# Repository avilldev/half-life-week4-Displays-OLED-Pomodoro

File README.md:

# BrainBreeze

A custom-built desktop hardware companion that tracks your study sessions and monitors your room's environment.

View the project on the [Half Life page](https://halflife.hackclub.com/projects/a25muen80i5c7zvo2wi1umca).

## What it is
ClimaFader merges a Pomodoro focus timer with real-time climate monitoring. You use a physical slide potentiometer to set the focus or break intervals, and tactile buttons to start, pause, or switch modes. The OLED screen displays your remaining time, accumulated "XP" (which are the completed sessions), and the current room temperature and humidity. When a session ends, a buzzer sounds an alert.

## Gallery

## BOM
| Component | Quantity |
| :--- | :---: |
| Seeed Studio XIAO RP2040 | 1 |
| 0.96" OLED Display (128x64, I2C) | 1 |
| AHT20 Temperature and Humidity Sensor | 1 |
| 60mm Slide Potentiometer | 1 |
| 6mm Tactile Push Button | 2 |
| Passive Buzzer | 1 |
| 4.7kΩ  Resistor | 2 |
| 100nF Ceramic Capacitor | 1 |
| 10uF Ceramic Capacitor | 1 |
| Custom PCB | 1 |

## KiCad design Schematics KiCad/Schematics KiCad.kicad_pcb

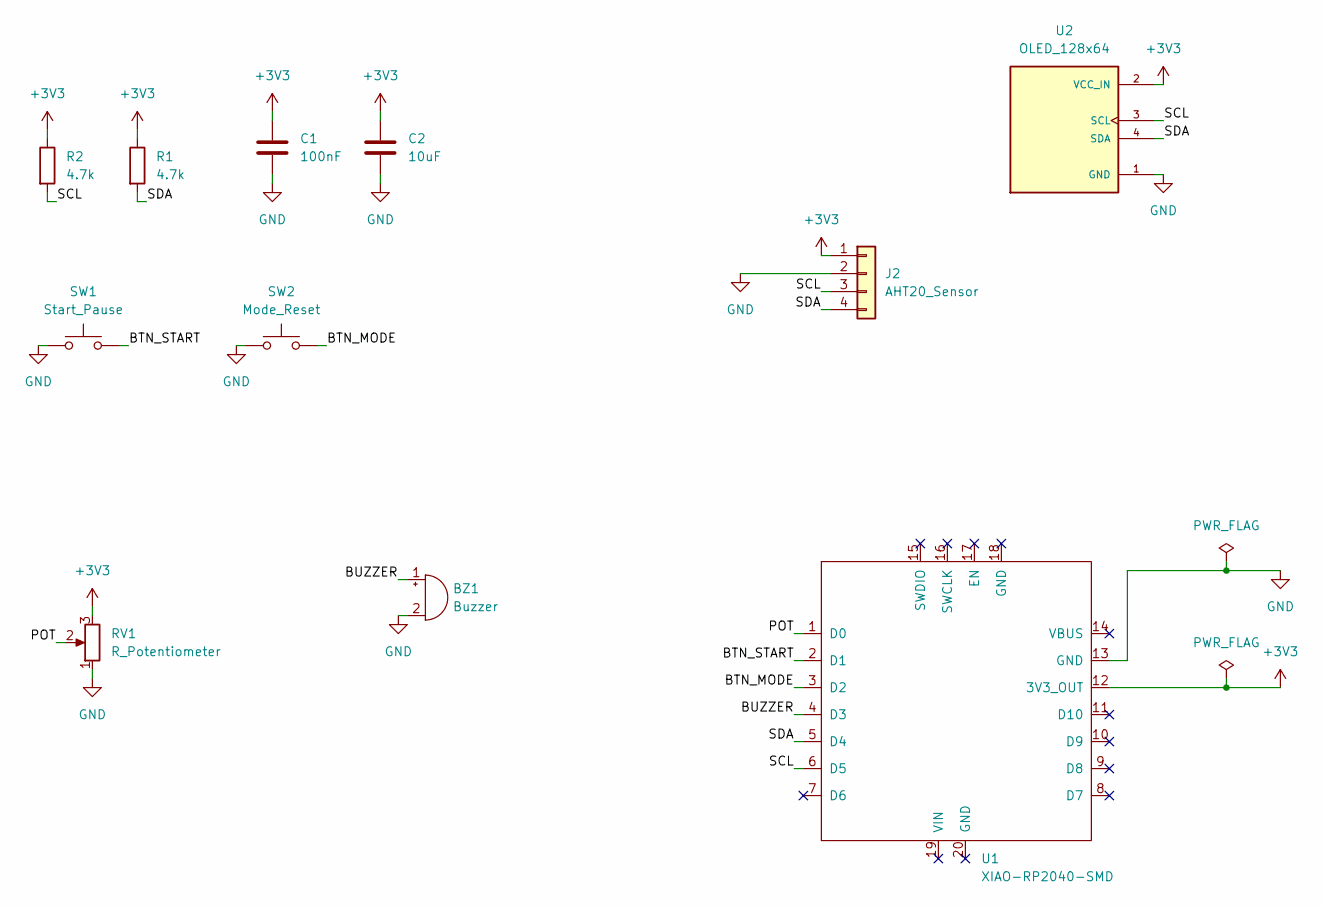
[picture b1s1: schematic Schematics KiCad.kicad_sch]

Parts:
BZ1: Buzzer; Buzzer_12x9.5RM7.6
C1: 100nF; C_Disc_D5.0mm_W2.5mm_P2.50mm
C2: 10uF; C_Disc_D5.0mm_W2.5mm_P2.50mm
J2: AHT20_Sensor; PinSocket_1x04_P2.54mm_Vertical
R1, R2: 4.7k; R_Axial_DIN0207_L6.3mm_D2.5mm_P7.62mm_Horizontal
RV1: R_Potentiometer; Potentiometer_Bourns_PTA6043_Single_Slide
SW1: Start_Pause; SW_PUSH_6mm
SW2: Mode_Reset; SW_PUSH_6mm
U1: XIAO-RP2040-SMD
U2: OLED_128x64; MODULE_DM-OLED096-636; PARTREV 2018-09-10

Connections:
+3V3: C1.1, C2.1, J2.1, R1.1, R2.1, RV1.3, U1.12 (3V3_OUT), U2.2 (VCC_IN)
/BTN_MODE: SW2.2, U1.3 (D2)
/BTN_START: SW1.2, U1.2 (D1)
/BUZZER: BZ1.1 (+), U1.4 (D3)
/POT: RV1.2, U1.1 (D0)
/SCL: J2.3, R2.2, U1.6 (D5), U2.3 (SCL)
/SDA: J2.4, R1.2, U1.5 (D4), U2.4 (SDA)
GND: BZ1.2 (-), C1.2, C2.2, J2.2, RV1.1, SW1.1, SW2.1, U1.13 (GND), U2.1 (GND)

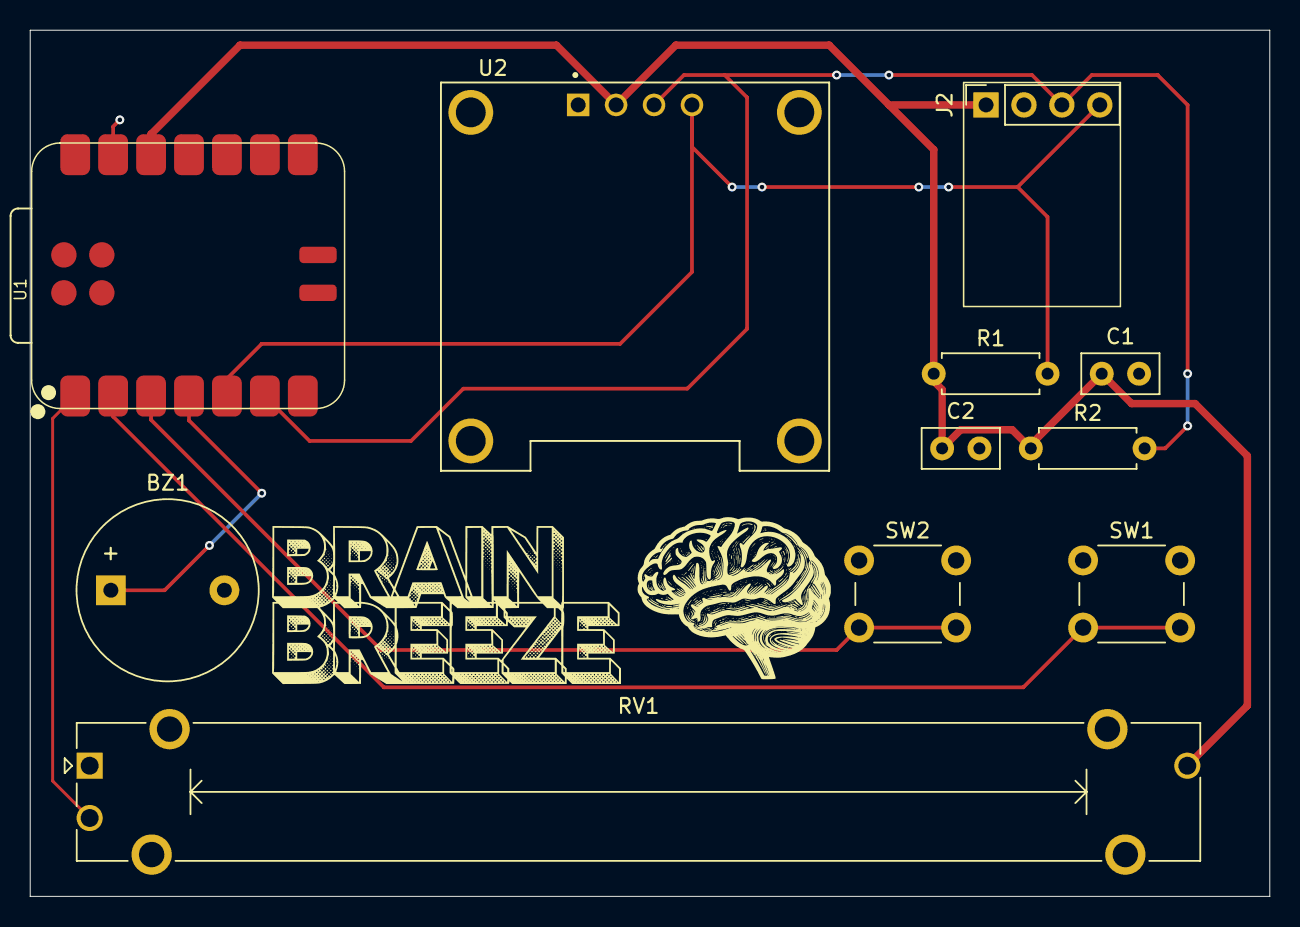
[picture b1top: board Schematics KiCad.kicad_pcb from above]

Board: 2 copper layers, 83.0 x 58.0 mm, 11 parts (0 on the bottom side), 8 nets.
